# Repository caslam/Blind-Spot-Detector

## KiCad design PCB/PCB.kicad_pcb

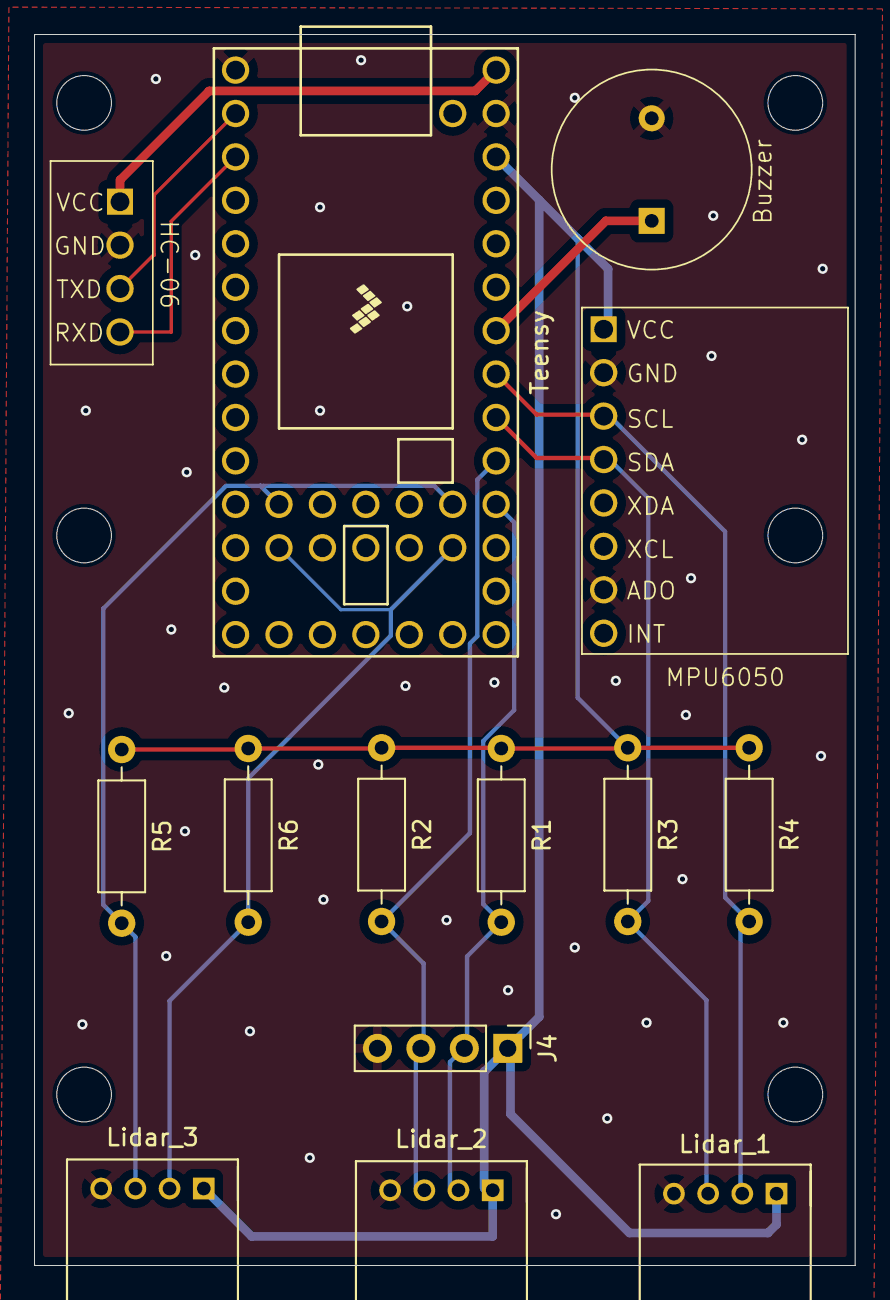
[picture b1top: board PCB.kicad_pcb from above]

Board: 4 copper layers, 48.0 x 72.0 mm, 14 parts (0 on the bottom side), 12 nets.

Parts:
Buzzer: Buzzer; Small_Buzzer
HC-06: HC-06_Module
J4: IMU_2; PinHeader_1x04_P2.54mm_Vertical
Lidar_1: Lidar_1; GROVE-HW4-2.0-90D
Lidar_2: Lidar_2; GROVE-HW4-2.0-90D
Lidar_3: Lidar_3; GROVE-HW4-2.0-90D
MPU6050: MPU6050_Module
R1, R2, R3, R4, R5, R6: 4.7k; R_Axial_DIN0207_L6.3mm_D2.5mm_P10.16mm_Horizontal
Teensy: Teensy4.0; Teensy40

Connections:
+3V3: J4.1, Lidar_1.1, Lidar_2.1, Lidar_3.1, MPU6050.1 (VCC), R1.1, R2.1, R3.1, R4.1, R5.1, R6.1, Teensy.31 (3V3)
+5V: HC-06.1 (VCC), Teensy.33 (VIN)
GND: Buzzer.2, HC-06.2 (GND), J4.4, Lidar_1.4, Lidar_2.4, Lidar_3.4, MPU6050.2 (GND), MPU6050.7 (ADO), Teensy.1 (GND), Teensy.32 (GND)
unnamed: HC-06.4 (RXD), Teensy.3 (1_TX1_CTX2_MISO1)
unnamed: HC-06.3 (TXD), Teensy.2 (0_RX1_CRX2_CS1)
unnamed: Lidar_1.2, MPU6050.3 (SCL), R4.2, Teensy.26 (19_A5_SCL0)
unnamed: Lidar_1.3, MPU6050.4 (SDA), R3.2, Teensy.25 (18_A4_SDA0)
unnamed: J4.2, Lidar_2.2, R1.2, Teensy.23 (16_A2_RX4_SCL1)
unnamed: J4.3, Lidar_2.3, R2.2, Teensy.24 (17_A3_TX4_SDA1)
unnamed: Lidar_3.2, R6.2, Teensy.35 (24_A10_TX6_SCL2), Teensy.43 (32_OUT1B)
unnamed: Lidar_3.3, R5.2, Teensy.36 (25_A11_RX6_SDA2), Teensy.44 (33_MCLK2)
unnamed: Buzzer.1, Teensy.27 (20_A6_TX5_LRCLK1)

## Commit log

2024-11-04 init
2024-11-04 David's screen layout
2024-11-12 PCB files
2024-11-13 test! added ability to change zone colors
2024-11-15 add pullups and second IMU
2024-11-15 gyro data sending
2024-11-18 mounting holes + vias, extra route for last I2C port
2024-11-18 vscode gitignore
2024-11-18 added Machine Learning files
2024-11-18 Added "Read Me" document
2024-11-19 added code that should feed in data to the model
2024-11-20 updated names and comments
2024-11-20 added arduino file
2024-11-20 New model header file, updated model .py code, renamed header files
2024-11-20 updated (forgot to include in the other push)
2024-11-22 parse sensor messages
2024-11-22 added IMU Arduino code w/ model
2024-11-22 added teensy_final Arduino file
2024-11-24 add gyro data checksum and fix lidar data parsing
2024-11-25 feeding combined gyro data to the ML model
2024-11-25 changed buzzer pin and IMU address to match PCB
2024-11-27 Tyler and Dat teensy updates
2024-11-27 work in progress; updating layout based on bluetooth input
2024-11-28 fixes & new write-to-file code
2024-11-28 added this back
2024-12-01 helmet-calibrated model
2024-12-01 updated & reorganized files
2024-12-01 added logs for troubleshooting, also testing new ways to trigger redraws
2024-12-01 fixing redraws (using new way of editing arrays)
2024-12-02 adding user input for username, hiding test functions
2024-12-02 flip zone colors
2024-12-02 fix phone gyro data y/z updates
2024-12-03 fixed app's distance icons & went back to last week's model
2024-12-03 add disconnect message and handle extra connects
2024-12-03 don't queue ML message toasts
2024-12-03 improve phone app message parsing
2024-12-03 smooth toasting
2024-12-04 updated easter eggs; added bluetooth status
2024-12-04 better ML output msg control for turning
2024-12-04 make textbox visible
2024-12-04 remove extra files
2024-12-09 Added comments
